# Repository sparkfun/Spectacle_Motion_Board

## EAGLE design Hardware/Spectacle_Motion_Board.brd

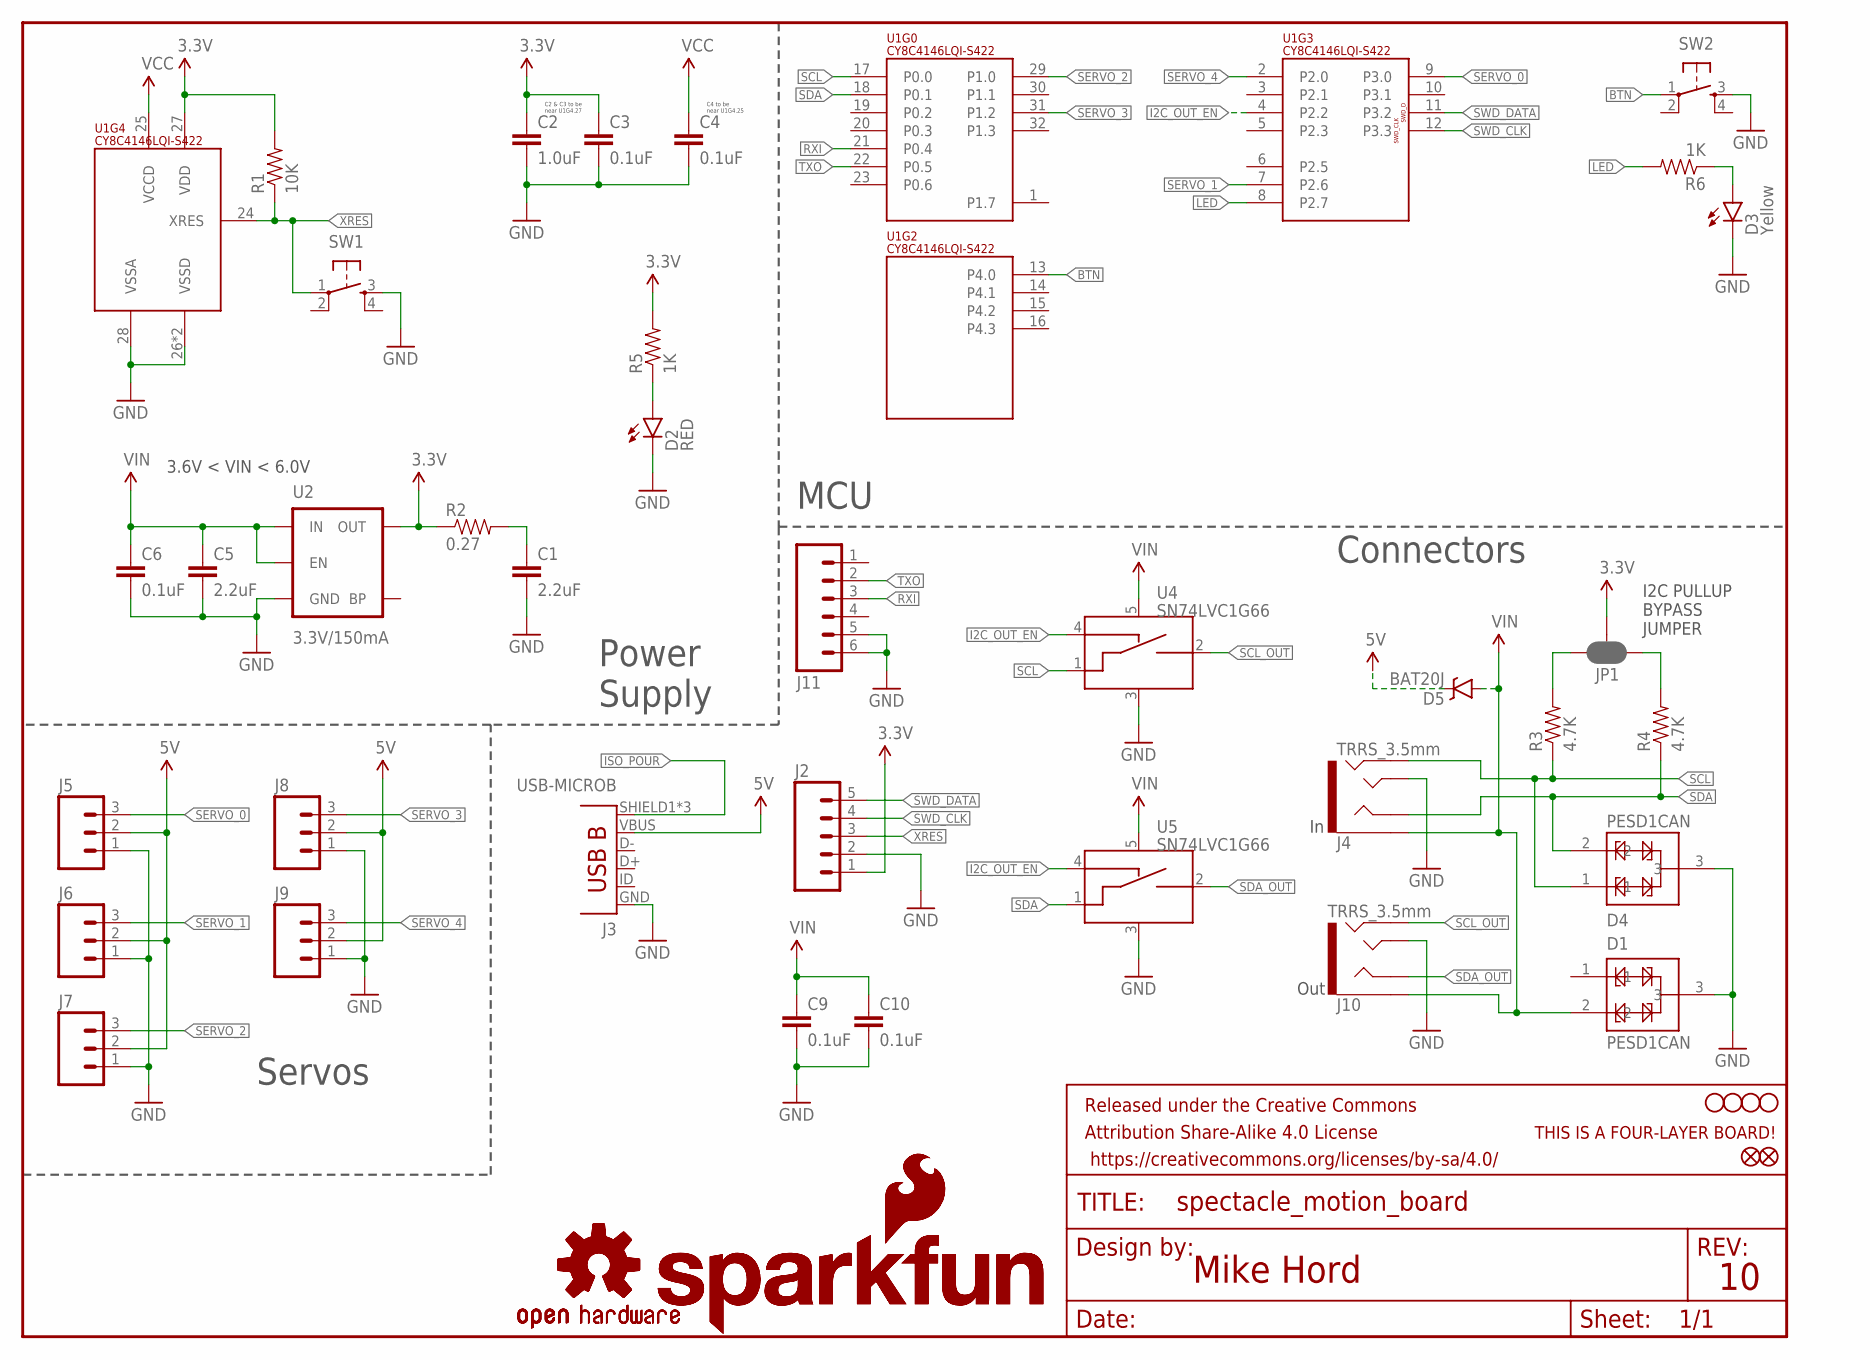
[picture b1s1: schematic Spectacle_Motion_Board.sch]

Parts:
C1, C5: 2.2uF; 0603-CAP
C2: 1.0uF; 0402-CAP
C3, C4, C6, C9, C10: 0.1uF; 0402-CAP
D1, D4: PESD1CAN; SOT23-3
D2: RED; LED-0603
D3: Yellow; LED-0603
D5: BAT20J; SOD-323
FD1, FD2: FIDUCIALUFIDUCIAL; MICRO-FIDUCIAL
FRAME1: FRAME-LETTER; CREATIVE_COMMONS
H1, H2, H3, H4: STAND-OFF
J2: M05NO_SILK; 1X05_NO_SILK
J3: USB-MICROB; USB-B-MICRO-SMD_V03_RED_PASTE
J4, J10: TRRS_3.5mm; AUDIO_JACK_3.5MM_TRRS_SMD_RA
J5, J6, J7, J8, J9: M03LOCK; 1X03_LOCK
J11: M06NO_SILK_NO_POP; 1X06_NO_SILK
JP1: JUMPER-PAD-3-NC_BY_PASTE; PAD-JUMPER-3-NC_BY_PASTE_YES_SILK_FULL_BOX
LOGO1, LOGO4: OSHW-LOGOS; OSHW-LOGO-S
LOGO2, LOGO3: SFE_LOGO_NAME_FLAME.1_INCH; SFE_LOGO_NAME_FLAME_.1
R1: 10K; 0603-RES
R2: 0.27; 0603-RES
R3, R4: 4.7K; 0603-RES
R5, R6: 1K; 0603-RES
SW1, SW2: SWITCH_SPST_4_PINRECT; TACTILE_SWITCH_SMD_4.6X2.8MM
U1: CY8C4146LQI-S422; QFN-32
U2: 3.3V/150mA; SOT23-5
U4, U5: SN74LVC1G66; SOT23-5
U$1: FOUR_LAYER_WARNING

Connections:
3.3V: C2.1, C3.1, J2.1, JP1.2, R1.2, R2.1, R5.2, U1.27 (VDD), U2.5 (OUT)
5V: D5.C, J3.VBUS, J5.2, J6.2, J7.2, J8.2, J9.2
BTN: SW2.1, U1.13 (P4.0)
GND: C1.2, C2.2, C3.2, C4.2, C5.2, C6.2, C9.2, C10.2, D1.3, D2.C, D3.C, D4.3, J2.2, J3.GND, J4.TIP, J5.1, J6.1, J7.1, J8.1, J9.1, J10.TIP, J11.5, J11.6, SW1.3, SW2.3, U1.26 (VSSD), U1.28 (VSSA), U1.EP (VSSD), U2.2 (GND), U4.3 (VSS), U5.3 (VSS)
I2C_OUT_EN: U1.4 (P2.2), U4.4 (CTRL_IN), U5.4 (CTRL_IN)
ISO_POUR: J3.SHIELD1 (SHIELD), J3.SHIELD2 (SHIELD), J3.SHIELD3 (SHIELD)
LED: R6.2, U1.8 (P2.7)
unnamed: JP1.3, R3.2
unnamed: C1.1, R2.2
unnamed: D2.A, R5.1
unnamed: D3.A, R6.1
unnamed: JP1.1, R4.2
RXI: J11.3, U1.21 (P0.4)
SCL: D4.1, J4.RING2, R3.1, U1.17 (P0.0), U4.1 (A_IN)
SCL_OUT: J10.RING2, U4.2 (A_OUT)
SDA: D4.2, J4.RING1, R4.1, U1.18 (P0.1), U5.1 (A_IN)
SDA_OUT: J10.RING1, U5.2 (A_OUT)
SERVO_0: J5.3, U1.9 (P3.0)
SERVO_1: J6.3, U1.7 (P2.6)
SERVO_2: J7.3, U1.29 (P1.0)
SERVO_3: J8.3, U1.31 (P1.2)
SERVO_4: J9.3, U1.2 (P2.0)
SWD_CLK: J2.4, U1.12 (P3.3)
SWD_DATA: J2.5, U1.11 (P3.2)
TXO: J11.2, U1.22 (P0.5)
VCC: C4.1, U1.25 (VCCD)
VIN: C5.1, C6.1, C9.1, C10.1, D1.2, D5.A, J4.EARTH, J10.EARTH, U2.1 (IN), U2.3 (EN), U4.5 (VCC), U5.5 (VCC)
XRES: J2.3, R1.1, SW1.1, U1.24 (XRES)

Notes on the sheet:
C2 & C3 to be near U1G4.27
C4 to be near U1G4.25
Mike Hord
MCU
Connectors
Servos
Power Supply
3.6V < VIN < 6.0V
I2C PULLUP BYPASS JUMPER
Out

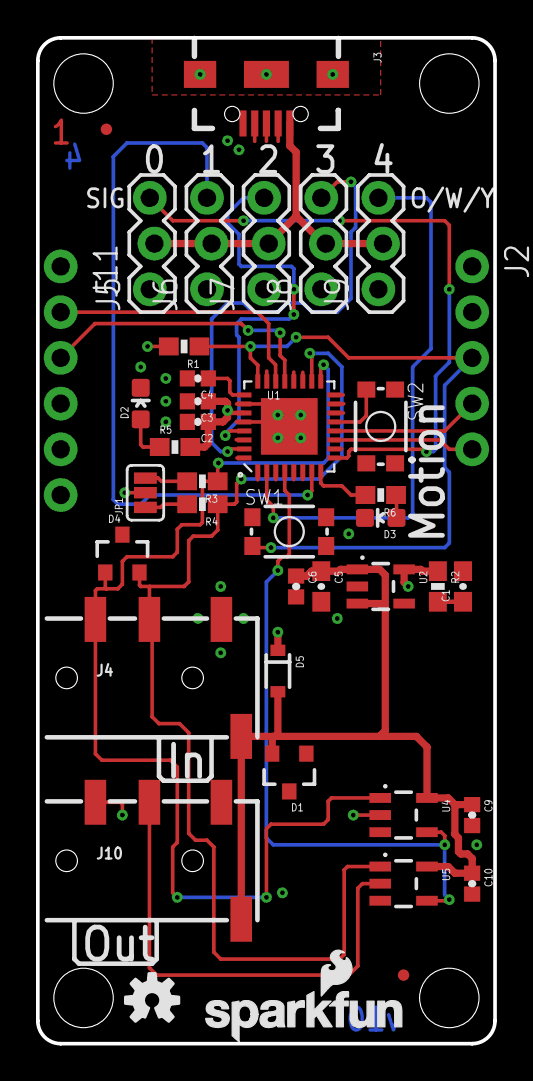
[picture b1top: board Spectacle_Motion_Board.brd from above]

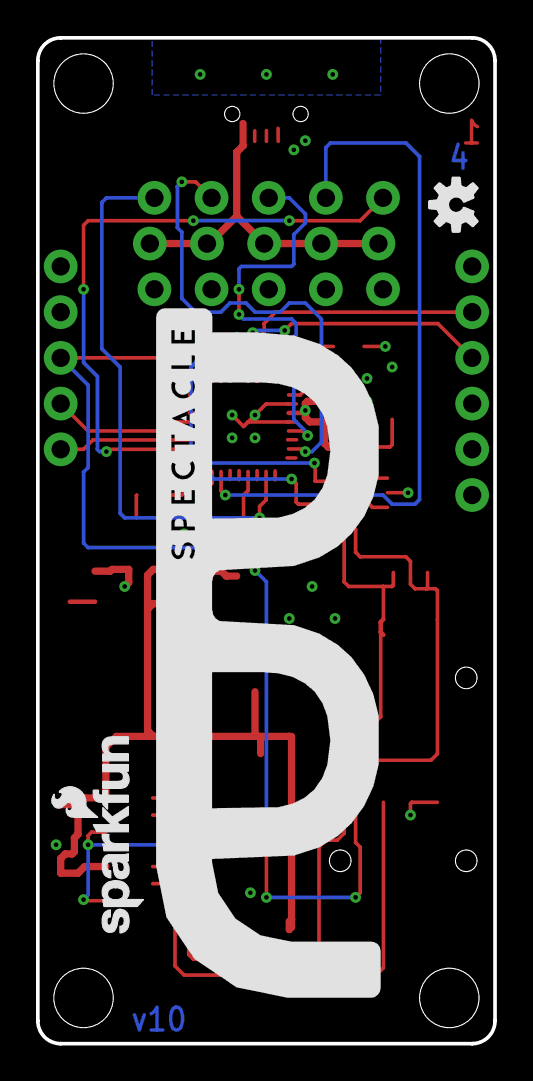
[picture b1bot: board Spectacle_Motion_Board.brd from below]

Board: 4 copper layers, 25.4 x 55.9 mm, 49 parts (3 on the bottom side), 28 nets.

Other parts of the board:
U$3: SPECTACLE_LOGO_NEGATIVE_1.5X0.5

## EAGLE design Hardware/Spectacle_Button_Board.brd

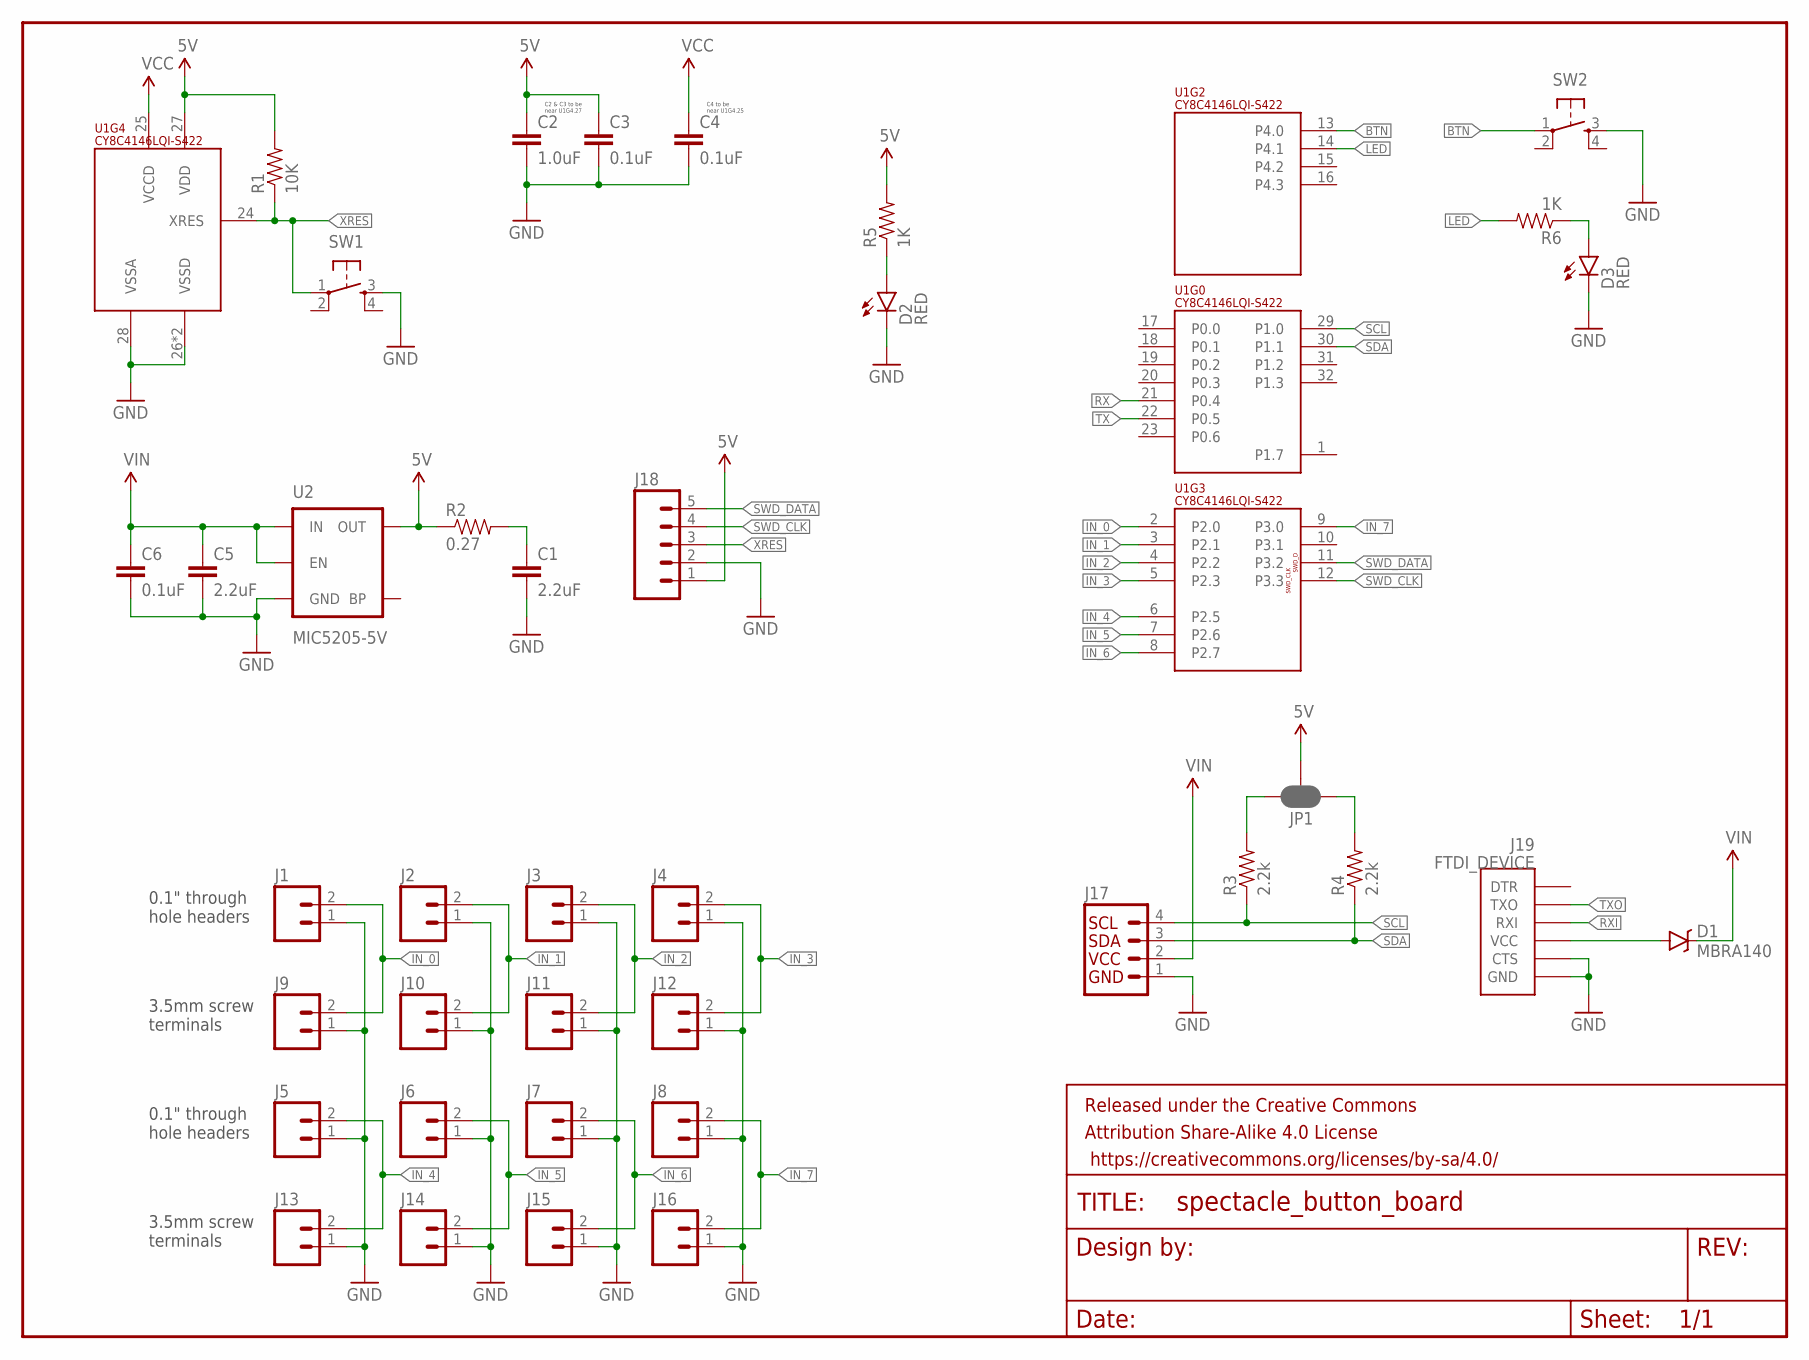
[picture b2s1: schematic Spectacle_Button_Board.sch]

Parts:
C1, C5: 2.2uF; 0603-CAP
C2: 1.0uF; 0402-CAP
C3, C4, C6: 0.1uF; 0402-CAP
D1: MBRA140; SMA-DIODE
D2, D3: RED; LED-0603
FRAME1: FRAME-LETTER; CREATIVE_COMMONS
J1, J2, J3, J4, J5, J6, J7, J8: M02PTH; 1X02
J9, J10, J11, J12, J13, J14, J15, J16: M023.5MM_LOCK; SCREWTERMINAL-3.5MM-2_LOCK
J17: I2C_STANDARD; 1X04
J18: M05PTH; 1X05
J19: FTDI_DEVICE; FTDI_DEVICE_SIDE
JP1: JUMPER-PAD-3-NC_BY_PASTE; PAD-JUMPER-3-NC_BY_PASTE_YES_SILK_FULL_BOX
R1: 10K; 0603-RES
R2: 0.27; 0603-RES
R3, R4: 2.2k; 0603-RES
R5, R6: 1K; 0603-RES
SW1, SW2: SWITCH_SPST_4_PINRECT; TACTILE_SWITCH_SMD_4.6X2.8MM
U1: CY8C4146LQI-S422; QFN-32
U2: MIC5205-5V; SOT23-5

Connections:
5V: C2.1, C3.1, J18.1, JP1.2, R1.2, R2.1, R5.2, U1.27 (VDD), U2.5 (OUT)
BTN: SW2.1, U1.13 (P4.0)
GND: C1.2, C2.2, C3.2, C4.2, C5.2, C6.2, D2.C, D3.C, J1.1, J2.1, J3.1, J4.1, J5.1, J6.1, J7.1, J8.1, J9.1, J10.1, J11.1, J12.1, J13.1, J14.1, J15.1, J16.1, J17.1, J18.2, J19.P$5 (CTS), J19.P$6 (GND), SW1.3, SW2.3, U1.26 (VSSD), U1.28 (VSSA), U1.EP (VSSD), U2.2 (GND)
IN_0: J1.2, J9.2, U1.2 (P2.0)
IN_1: J2.2, J10.2, U1.3 (P2.1)
IN_2: J3.2, J11.2, U1.4 (P2.2)
IN_3: J4.2, J12.2, U1.5 (P2.3)
IN_4: J5.2, J13.2, U1.6 (P2.5)
IN_5: J6.2, J14.2, U1.7 (P2.6)
IN_6: J7.2, J15.2, U1.8 (P2.7)
IN_7: J8.2, J16.2, U1.9 (P3.0)
LED: R6.2, U1.14 (P4.1)
unnamed: D1.A, J19.P$4 (VCC)
unnamed: JP1.3, R3.2
unnamed: C1.1, R2.2
unnamed: D2.A, R5.1
unnamed: D3.A, R6.1
unnamed: JP1.1, R4.2
RX: U1.21 (P0.4)
RXI: J19.P$3 (RXI)
SCL: J17.4, R3.1, U1.29 (P1.0)
SDA: J17.3, R4.1, U1.30 (P1.1)
SWD_CLK: J18.4, U1.12 (P3.3)
SWD_DATA: J18.5, U1.11 (P3.2)
TX: U1.22 (P0.5)
TXO: J19.P$2 (TXO)
VCC: C4.1, U1.25 (VCCD)
VIN: C5.1, C6.1, D1.C, J17.2, U2.1 (IN), U2.3 (EN)
XRES: J18.3, R1.1, SW1.1, U1.24 (XRES)

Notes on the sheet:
3.5mm screw terminals
0.1" through hole headers
C2 & C3 to be near U1G4.27
C4 to be near U1G4.25

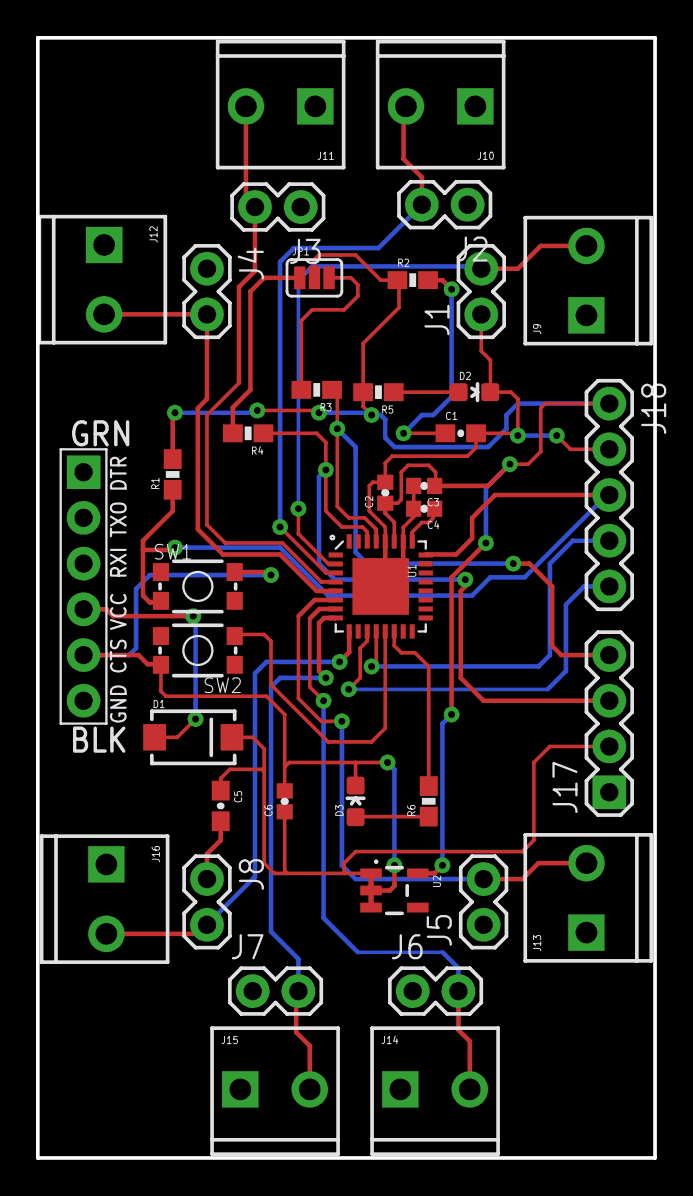
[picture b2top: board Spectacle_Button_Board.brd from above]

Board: 2 copper layers, 34.3 x 62.2 mm, 40 parts (0 on the bottom side), 25 nets.

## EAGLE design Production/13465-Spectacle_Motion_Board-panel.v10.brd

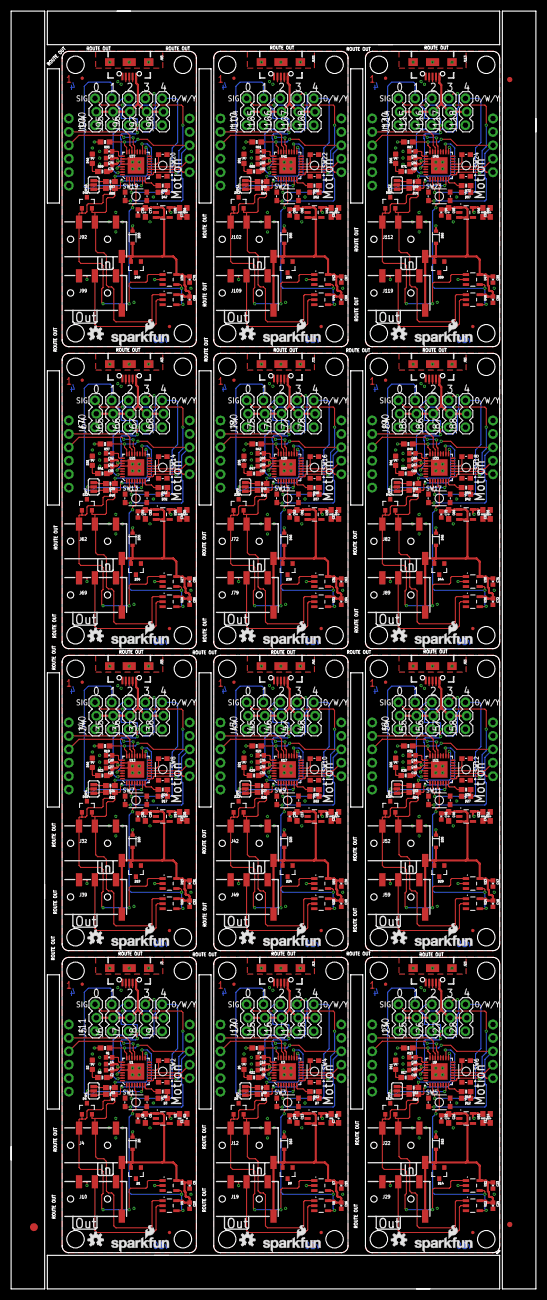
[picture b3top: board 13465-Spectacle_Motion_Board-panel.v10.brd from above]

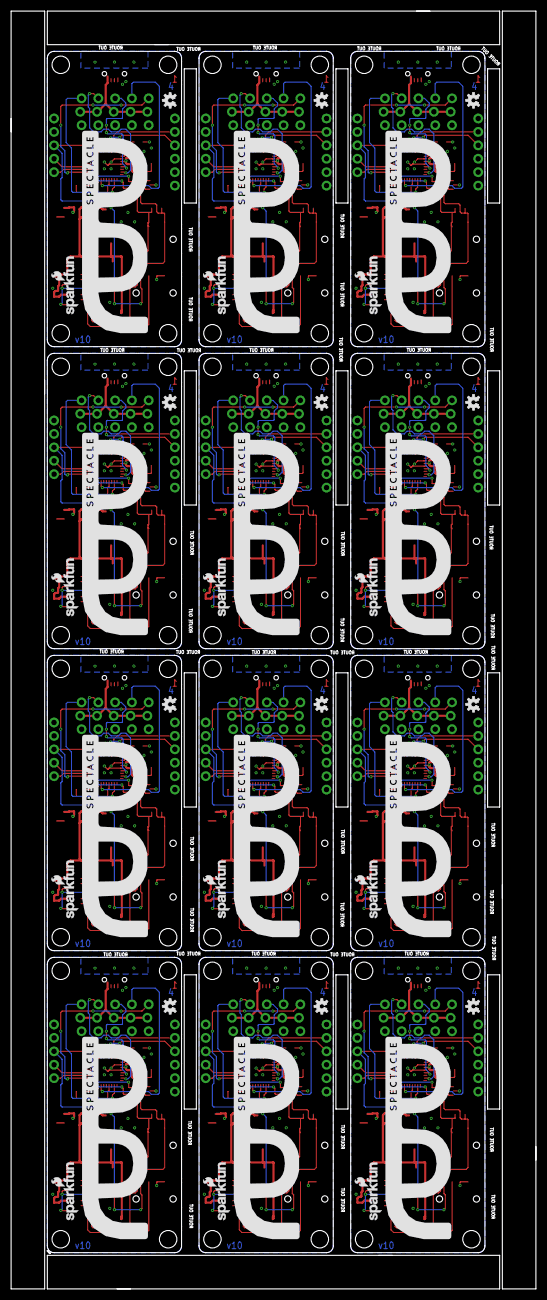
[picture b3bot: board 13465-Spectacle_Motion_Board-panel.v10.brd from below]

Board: 4 copper layers, 99.3 x 241.8 mm, 567 parts (36 on the bottom side), 336 nets.

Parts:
C1, C5, C7, C13, C17, C21, C25, C29, C33, C37, C41, C45, C49, C53, C57, C61, C65, C69, C73, C77, C81, C85, C89, C93: 2.2uF; 0603-CAP
C2, C8, C18, C26, C34, C42, C50, C58, C66, C74, C82, C90: 1.0uF; 0402-CAP
C3, C4, C6, C9, C10, C11, C12, C14, C15, C16, C19, C20, C22, C23, C24, C27, C28, C30, C31, C32, C35, C36, C38, C39, C40, C43, C44, C46, C47, C48, C51, C52, C54, C55, C56, C59, C60, C62, C63, C64, C67, C68, C70, C71, C72, C75, C76, C78, C79, C80, C83, C84, C86, C87, C88, C91, C92, C94, C95, C96: 0.1uF; 0402-CAP
D1, D4, D8, D9, D13, D14, D18, D19, D23, D24, D28, D29, D33, D34, D38, D39, D43, D44, D48, D49, D53, D54, D58, D59: PESD1CAN; SOT23-3
D2, D6, D11, D16, D21, D26, D31, D36, D41, D46, D51, D56: RED; LED-0603
D3, D7, D12, D17, D22, D27, D32, D37, D42, D47, D52, D57: Yellow; LED-0603
D5, D10, D15, D20, D25, D30, D35, D40, D45, D50, D55, D60: BAT20J; SOD-323
E$1: FIDUCIAL-1.5X3
E$7, E$8: FIDUCIAL-1X2
FD1, FD2, FD3, FD4, FD5, FD6, FD7, FD8, FD9, FD10, FD11, FD12, FD13, FD14, FD15, FD16, FD17, FD18, FD19, FD20, FD21, FD22, FD23, FD24: FIDUCIALUFIDUCIAL; MICRO-FIDUCIAL
H1, H2, H3, H4, H5, H6, H7, H8, H9, H10, H11, H12, H13, H14, H15, H16, H17, H18, H19, H20, H21, H22, H23, H24, H25, H26, H27, H28, H29, H30, H31, H32, H33, H34, H35, H36, H37, H38, H39, H40, H41, H42, H43, H44, H45, H46, H47, H48: STAND-OFF
J1, J2, J21, J31, J41, J51, J61, J71, J81, J91, J101, J111: 1X05_NO_SILK
J3, J13, J23, J33, J43, J53, J63, J73, J83, J93, J103, J113: USB-MICROB; USB-B-MICRO-SMD_V03_RED_PASTE
J4, J10, J12, J19, J22, J29, J32, J39, J42, J49, J52, J59, J62, J69, J72, J79, J82, J89, J92, J99, J102, J109, J112, J119: TRRS_3.5mm; AUDIO_JACK_3.5MM_TRRS_SMD_RA
J5, J6, J7, J8, J9, J14, J15, J16, J17, J18, J24, J25, J26, J27, J28, J34, J35, J36, J37, J38, J44, J45, J46, J47, J48, J54, J55, J56, J57, J58, J64, J65, J66, J67, J68, J74, J75, J76, J77, J78, J84, J85, J86, J87, J88, J94, J95, J96, J97, J98, J104, J105, J106, J107, J108, J114, J115, J116, J117, J118: 1X03_LOCK
J11, J20, J30, J40, J50, J60, J70, J80, J90, J100, J110, J120: 1X06_NO_SILK
JP1, JP2, JP3, JP4, JP5, JP6, JP7, JP8, JP9, JP10, JP11, JP12: JUMPER-PAD-3-NC_BY_PASTE; PAD-JUMPER-3-NC_BY_PASTE_YES_SILK_FULL_BOX
LOGO1, LOGO4, LOGO5, LOGO8, LOGO9, LOGO12, LOGO13, LOGO16, LOGO17, LOGO20, LOGO21, LOGO24, LOGO25, LOGO28, LOGO29, LOGO32, LOGO33, LOGO36, LOGO37, LOGO40, LOGO41, LOGO44, LOGO45, LOGO48: OSHW-LOGOS; OSHW-LOGO-S
LOGO2, LOGO3, LOGO6, LOGO7, LOGO10, LOGO11, LOGO14, LOGO15, LOGO18, LOGO19, LOGO22, LOGO23, LOGO26, LOGO27, LOGO30, LOGO31, LOGO34, LOGO35, LOGO38, LOGO39, LOGO42, LOGO43, LOGO46, LOGO47: SFE_LOGO_NAME_FLAME.1_INCH; SFE_LOGO_NAME_FLAME_.1
R1, R7, R13, R19, R25, R31, R37, R43, R49, R55, R61, R67: 10K; 0603-RES
R2, R8, R14, R20, R26, R32, R38, R44, R50, R56, R62, R68: 0.27; 0603-RES
R3, R4, R9, R10, R15, R16, R21, R22, R27, R28, R33, R34, R39, R40, R45, R46, R51, R52, R57, R58, R63, R64, R69, R70: 4.7K; 0603-RES
R5, R6, R11, R12, R17, R18, R23, R24, R29, R30, R35, R36, R41, R42, R47, R48, R53, R54, R59, R60, R65, R66, R71, R72: 1K; 0603-RES
SW1, SW2, SW3, SW4, SW5, SW6, SW7, SW8, SW9, SW10, SW11, SW12, SW13, SW14, SW15, SW16, SW17, SW18, SW19, SW20, SW21, SW22, SW23, SW24: TACTILE_SWITCH_SMD_4.6X2.8MM
U1, U3, U9, U13, U17, U21, U25, U29, U33, U37, U41, U45: CY8C4146LQI-S422; QFN-32
U2, U6, U10, U14, U18, U22, U26, U30, U34, U38, U42, U46: 3.3V/150mA; SOT23-5
U4, U5, U7, U8, U11, U12, U15, U16, U19, U20, U23, U24, U27, U28, U31, U32, U35, U36, U39, U40, U43, U44, U47, U48: SN74LVC1G66; SOT23-5
U$1, U$2, U$3, U$4, U$5, U$6, U$7, U$8, U$9, U$10, U$11, U$12: SPECTACLE_LOGO_NEGATIVE_1.5X0.5

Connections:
3.3V: C2.1, C3.1, J2.1, JP1.2, R1.2, R2.1, R5.2, U1.27, U2.5
3.3V1: C8.1, C11.1, J1.1, JP2.2, R7.2, R8.1, R11.2, U3.27, U6.5
3.3V2: C18.1, C19.1, J21.1, JP3.2, R13.2, R14.1, R17.2, U9.27, U10.5
3.3V3: C26.1, C27.1, J31.1, JP4.2, R19.2, R20.1, R23.2, U13.27, U14.5
3.3V4: C34.1, C35.1, J41.1, JP5.2, R25.2, R26.1, R29.2, U17.27, U18.5
3.3V5: C42.1, C43.1, J51.1, JP6.2, R31.2, R32.1, R35.2, U21.27, U22.5
3.3V6: C50.1, C51.1, J61.1, JP7.2, R37.2, R38.1, R41.2, U25.27, U26.5
3.3V7: C58.1, C59.1, J71.1, JP8.2, R43.2, R44.1, R47.2, U29.27, U30.5
3.3V8: C66.1, C67.1, J81.1, JP9.2, R49.2, R50.1, R53.2, U33.27, U34.5
3.3V9: C74.1, C75.1, J91.1, JP10.2, R55.2, R56.1, R59.2, U37.27, U38.5
3.3V10: C82.1, C83.1, J101.1, JP11.2, R61.2, R62.1, R65.2, U41.27, U42.5
3.3V11: C90.1, C91.1, J111.1, JP12.2, R67.2, R68.1, R71.2, U45.27, U46.5
5V: D5.C, J3.VBUS, J5.2, J6.2, J7.2, J8.2, J9.2
5V1: D10.C, J13.VBUS, J14.2, J15.2, J16.2, J17.2, J18.2
5V2: D15.C, J23.VBUS, J24.2, J25.2, J26.2, J27.2, J28.2
5V3: D20.C, J33.VBUS, J34.2, J35.2, J36.2, J37.2, J38.2
5V4: D25.C, J43.VBUS, J44.2, J45.2, J46.2, J47.2, J48.2
5V5: D30.C, J53.VBUS, J54.2, J55.2, J56.2, J57.2, J58.2
5V6: D35.C, J63.VBUS, J64.2, J65.2, J66.2, J67.2, J68.2
5V7: D40.C, J73.VBUS, J74.2, J75.2, J76.2, J77.2, J78.2
5V8: D45.C, J83.VBUS, J84.2, J85.2, J86.2, J87.2, J88.2
5V9: D50.C, J93.VBUS, J94.2, J95.2, J96.2, J97.2, J98.2
5V10: D55.C, J103.VBUS, J104.2, J105.2, J106.2, J107.2, J108.2
5V11: D60.C, J113.VBUS, J114.2, J115.2, J116.2, J117.2, J118.2
BTN: SW2.1, U1.13
BTN1: SW4.1, U3.13
BTN2: SW6.1, U9.13
BTN3: SW8.1, U13.13
BTN4: SW10.1, U17.13
BTN5: SW12.1, U21.13
BTN6: SW14.1, U25.13
BTN7: SW16.1, U29.13
BTN8: SW18.1, U33.13
BTN9: SW20.1, U37.13
BTN10: SW22.1, U41.13
BTN11: SW24.1, U45.13
GND: C1.2, C2.2, C3.2, C4.2, C5.2, C6.2, C9.2, C10.2, D1.3, D2.C, D3.C, D4.3, J2.2, J3.GND, J4.TIP, J5.1, J6.1, J7.1, J8.1, J9.1, J10.TIP, J11.5, J11.6, SW1.3, SW2.3, U1.26, U1.28, U1.EP, U2.2, U4.3, U5.3
GND1: C7.2, C8.2, C11.2, C12.2, C13.2, C14.2, C15.2, C16.2, D6.C, D7.C, D8.3, D9.3, J1.2, J12.TIP, J13.GND, J14.1, J15.1, J16.1, J17.1, J18.1, J19.TIP, J20.5, J20.6, SW3.3, SW4.3, U3.26, U3.28, U3.EP, U6.2, U7.3, U8.3
GND2: C17.2, C18.2, C19.2, C20.2, C21.2, C22.2, C23.2, C24.2, D11.C, D12.C, D13.3, D14.3, J21.2, J22.TIP, J23.GND, J24.1, J25.1, J26.1, J27.1, J28.1, J29.TIP, J30.5, J30.6, SW5.3, SW6.3, U9.26, U9.28, U9.EP, U10.2, U11.3, U12.3
GND3: C25.2, C26.2, C27.2, C28.2, C29.2, C30.2, C31.2, C32.2, D16.C, D17.C, D18.3, D19.3, J31.2, J32.TIP, J33.GND, J34.1, J35.1, J36.1, J37.1, J38.1, J39.TIP, J40.5, J40.6, SW7.3, SW8.3, U13.26, U13.28, U13.EP, U14.2, U15.3, U16.3
GND4: C33.2, C34.2, C35.2, C36.2, C37.2, C38.2, C39.2, C40.2, D21.C, D22.C, D23.3, D24.3, J41.2, J42.TIP, J43.GND, J44.1, J45.1, J46.1, J47.1, J48.1, J49.TIP, J50.5, J50.6, SW9.3, SW10.3, U17.26, U17.28, U17.EP, U18.2, U19.3, U20.3
GND5: C41.2, C42.2, C43.2, C44.2, C45.2, C46.2, C47.2, C48.2, D26.C, D27.C, D28.3, D29.3, J51.2, J52.TIP, J53.GND, J54.1, J55.1, J56.1, J57.1, J58.1, J59.TIP, J60.5, J60.6, SW11.3, SW12.3, U21.26, U21.28, U21.EP, U22.2, U23.3, U24.3
GND6: C49.2, C50.2, C51.2, C52.2, C53.2, C54.2, C55.2, C56.2, D31.C, D32.C, D33.3, D34.3, J61.2, J62.TIP, J63.GND, J64.1, J65.1, J66.1, J67.1, J68.1, J69.TIP, J70.5, J70.6, SW13.3, SW14.3, U25.26, U25.28, U25.EP, U26.2, U27.3, U28.3
GND7: C57.2, C58.2, C59.2, C60.2, C61.2, C62.2, C63.2, C64.2, D36.C, D37.C, D38.3, D39.3, J71.2, J72.TIP, J73.GND, J74.1, J75.1, J76.1, J77.1, J78.1, J79.TIP, J80.5, J80.6, SW15.3, SW16.3, U29.26, U29.28, U29.EP, U30.2, U31.3, U32.3
GND8: C65.2, C66.2, C67.2, C68.2, C69.2, C70.2, C71.2, C72.2, D41.C, D42.C, D43.3, D44.3, J81.2, J82.TIP, J83.GND, J84.1, J85.1, J86.1, J87.1, J88.1, J89.TIP, J90.5, J90.6, SW17.3, SW18.3, U33.26, U33.28, U33.EP, U34.2, U35.3, U36.3
GND9: C73.2, C74.2, C75.2, C76.2, C77.2, C78.2, C79.2, C80.2, D46.C, D47.C, D48.3, D49.3, J91.2, J92.TIP, J93.GND, J94.1, J95.1, J96.1, J97.1, J98.1, J99.TIP, J100.5, J100.6, SW19.3, SW20.3, U37.26, U37.28, U37.EP, U38.2, U39.3, U40.3
GND10: C81.2, C82.2, C83.2, C84.2, C85.2, C86.2, C87.2, C88.2, D51.C, D52.C, D53.3, D54.3, J101.2, J102.TIP, J103.GND, J104.1, J105.1, J106.1, J107.1, J108.1, J109.TIP, J110.5, J110.6, SW21.3, SW22.3, U41.26, U41.28, U41.EP, U42.2, U43.3, U44.3
GND11: C89.2, C90.2, C91.2, C92.2, C93.2, C94.2, C95.2, C96.2, D56.C, D57.C, D58.3, D59.3, J111.2, J112.TIP, J113.GND, J114.1, J115.1, J116.1, J117.1, J118.1, J119.TIP, J120.5, J120.6, SW23.3, SW24.3, U45.26, U45.28, U45.EP, U46.2, U47.3, U48.3
I2C_OUT_EN: U1.4, U4.4, U5.4
I2C_OUT_EN1: U3.4, U7.4, U8.4
I2C_OUT_EN2: U9.4, U11.4, U12.4
I2C_OUT_EN3: U13.4, U15.4, U16.4
I2C_OUT_EN4: U17.4, U19.4, U20.4
I2C_OUT_EN5: U21.4, U23.4, U24.4
I2C_OUT_EN6: U25.4, U27.4, U28.4
I2C_OUT_EN7: U29.4, U31.4, U32.4
I2C_OUT_EN8: U33.4, U35.4, U36.4
I2C_OUT_EN9: U37.4, U39.4, U40.4
I2C_OUT_EN10: U41.4, U43.4, U44.4
I2C_OUT_EN11: U45.4, U47.4, U48.4
ISO_POUR: J3.SHIELD1, J3.SHIELD2, J3.SHIELD3
ISO_POUR1: J13.SHIELD1, J13.SHIELD2, J13.SHIELD3
ISO_POUR2: J23.SHIELD1, J23.SHIELD2, J23.SHIELD3
ISO_POUR3: J33.SHIELD1, J33.SHIELD2, J33.SHIELD3
ISO_POUR4: J43.SHIELD1, J43.SHIELD2, J43.SHIELD3
ISO_POUR5: J53.SHIELD1, J53.SHIELD2, J53.SHIELD3
ISO_POUR6: J63.SHIELD1, J63.SHIELD2, J63.SHIELD3
ISO_POUR7: J73.SHIELD1, J73.SHIELD2, J73.SHIELD3
ISO_POUR8: J83.SHIELD1, J83.SHIELD2, J83.SHIELD3
ISO_POUR9: J93.SHIELD1, J93.SHIELD2, J93.SHIELD3
ISO_POUR10: J103.SHIELD1, J103.SHIELD2, J103.SHIELD3
ISO_POUR11: J113.SHIELD1, J113.SHIELD2, J113.SHIELD3
LED: R6.2, U1.8
LED1: R12.2, U3.8
LED2: R18.2, U9.8
LED3: R24.2, U13.8
LED4: R30.2, U17.8
LED5: R36.2, U21.8
LED6: R42.2, U25.8
LED7: R48.2, U29.8
LED8: R54.2, U33.8
LED9: R60.2, U37.8
LED10: R66.2, U41.8
LED11: R72.2, U45.8
unnamed: JP1.3, R3.2
unnamed: C1.1, R2.2
unnamed: D2.A, R5.1
unnamed: D3.A, R6.1
unnamed: JP1.1, R4.2
unnamed: C7.1, R8.2
unnamed: JP2.3, R9.2
unnamed: JP2.1, R10.2
unnamed: D6.A, R11.1
unnamed: D7.A, R12.1
unnamed: C17.1, R14.2
unnamed: JP3.3, R15.2
unnamed: JP3.1, R16.2
unnamed: D11.A, R17.1
unnamed: D12.A, R18.1
unnamed: C25.1, R20.2
unnamed: JP4.3, R21.2
unnamed: JP4.1, R22.2
unnamed: D16.A, R23.1
unnamed: D17.A, R24.1
unnamed: C33.1, R26.2
unnamed: JP5.3, R27.2
unnamed: JP5.1, R28.2
unnamed: D21.A, R29.1
unnamed: D22.A, R30.1
unnamed: C41.1, R32.2
unnamed: JP6.3, R33.2
unnamed: JP6.1, R34.2
unnamed: D26.A, R35.1
unnamed: D27.A, R36.1
unnamed: C49.1, R38.2
unnamed: JP7.3, R39.2
unnamed: JP7.1, R40.2
unnamed: D31.A, R41.1
unnamed: D32.A, R42.1
unnamed: C57.1, R44.2
unnamed: JP8.3, R45.2
unnamed: JP8.1, R46.2
unnamed: D36.A, R47.1
unnamed: D37.A, R48.1
unnamed: C65.1, R50.2
unnamed: JP9.3, R51.2
unnamed: JP9.1, R52.2
unnamed: D41.A, R53.1
unnamed: D42.A, R54.1
unnamed: C73.1, R56.2
unnamed: JP10.3, R57.2
unnamed: JP10.1, R58.2
unnamed: D46.A, R59.1
unnamed: D47.A, R60.1
unnamed: C81.1, R62.2
unnamed: JP11.3, R63.2
unnamed: JP11.1, R64.2
unnamed: D51.A, R65.1
unnamed: D52.A, R66.1
unnamed: C89.1, R68.2
unnamed: JP12.3, R69.2
unnamed: JP12.1, R70.2
unnamed: D56.A, R71.1
unnamed: D57.A, R72.1
RXI: J11.3, U1.21
RXI1: J20.3, U3.21
RXI2: J30.3, U9.21
RXI3: J40.3, U13.21
RXI4: J50.3, U17.21
RXI5: J60.3, U21.21
RXI6: J70.3, U25.21
RXI7: J80.3, U29.21
RXI8: J90.3, U33.21
RXI9: J100.3, U37.21
RXI10: J110.3, U41.21
RXI11: J120.3, U45.21
SCL: D4.1, J4.RING2, R3.1, U1.17, U4.1
SCL1: D8.1, J12.RING2, R9.1, U3.17, U7.1
SCL2: D13.1, J22.RING2, R15.1, U9.17, U11.1
SCL3: D18.1, J32.RING2, R21.1, U13.17, U15.1
SCL4: D23.1, J42.RING2, R27.1, U17.17, U19.1
SCL5: D28.1, J52.RING2, R33.1, U21.17, U23.1
SCL6: D33.1, J62.RING2, R39.1, U25.17, U27.1
SCL7: D38.1, J72.RING2, R45.1, U29.17, U31.1
SCL8: D43.1, J82.RING2, R51.1, U33.17, U35.1
SCL9: D48.1, J92.RING2, R57.1, U37.17, U39.1
SCL10: D53.1, J102.RING2, R63.1, U41.17, U43.1
SCL11: D58.1, J112.RING2, R69.1, U45.17, U47.1
SCL_OUT: J10.RING2, U4.2
SCL_OUT1: J19.RING2, U7.2
SCL_OUT2: J29.RING2, U11.2
SCL_OUT3: J39.RING2, U15.2
SCL_OUT4: J49.RING2, U19.2
SCL_OUT5: J59.RING2, U23.2
SCL_OUT6: J69.RING2, U27.2
SCL_OUT7: J79.RING2, U31.2
SCL_OUT8: J89.RING2, U35.2
SCL_OUT9: J99.RING2, U39.2
SCL_OUT10: J109.RING2, U43.2
SCL_OUT11: J119.RING2, U47.2
SDA: D4.2, J4.RING1, R4.1, U1.18, U5.1
SDA1: D8.2, J12.RING1, R10.1, U3.18, U8.1
SDA2: D13.2, J22.RING1, R16.1, U9.18, U12.1
SDA3: D18.2, J32.RING1, R22.1, U13.18, U16.1
SDA4: D23.2, J42.RING1, R28.1, U17.18, U20.1
SDA5: D28.2, J52.RING1, R34.1, U21.18, U24.1
SDA6: D33.2, J62.RING1, R40.1, U25.18, U28.1
SDA7: D38.2, J72.RING1, R46.1, U29.18, U32.1
SDA8: D43.2, J82.RING1, R52.1, U33.18, U36.1
SDA9: D48.2, J92.RING1, R58.1, U37.18, U40.1
SDA10: D53.2, J102.RING1, R64.1, U41.18, U44.1
SDA11: D58.2, J112.RING1, R70.1, U45.18, U48.1
SDA_OUT: J10.RING1, U5.2
SDA_OUT1: J19.RING1, U8.2
SDA_OUT2: J29.RING1, U12.2
SDA_OUT3: J39.RING1, U16.2
SDA_OUT4: J49.RING1, U20.2
SDA_OUT5: J59.RING1, U24.2
SDA_OUT6: J69.RING1, U28.2
SDA_OUT7: J79.RING1, U32.2
SDA_OUT8: J89.RING1, U36.2
SDA_OUT9: J99.RING1, U40.2
SDA_OUT10: J109.RING1, U44.2
SDA_OUT11: J119.RING1, U48.2
SERVO_0: J5.3, U1.9
SERVO_1: J6.3, U1.7
SERVO_2: J7.3, U1.29
SERVO_3: J8.3, U1.31
SERVO_4: J9.3, U1.2
SERVO_5: J14.3, U3.9
SERVO_6: J15.3, U3.7
SERVO_7: J16.3, U3.29
SERVO_8: J17.3, U3.31
SERVO_9: J18.3, U3.2
SERVO_10: J24.3, U9.9
SERVO_11: J25.3, U9.7
SERVO_12: J26.3, U9.29
SERVO_13: J27.3, U9.31
SERVO_14: J28.3, U9.2
SERVO_15: J34.3, U13.9
SERVO_16: J35.3, U13.7
SERVO_17: J36.3, U13.29
SERVO_18: J37.3, U13.31
SERVO_19: J38.3, U13.2
SERVO_20: J44.3, U17.9
SERVO_21: J45.3, U17.7
SERVO_22: J46.3, U17.29
SERVO_23: J47.3, U17.31
SERVO_24: J48.3, U17.2
SERVO_25: J54.3, U21.9
SERVO_26: J55.3, U21.7
SERVO_27: J56.3, U21.29
SERVO_28: J57.3, U21.31
SERVO_29: J58.3, U21.2
SERVO_30: J64.3, U25.9
SERVO_31: J65.3, U25.7
SERVO_32: J66.3, U25.29
SERVO_33: J67.3, U25.31
SERVO_34: J68.3, U25.2
SERVO_35: J74.3, U29.9
SERVO_36: J75.3, U29.7
SERVO_37: J76.3, U29.29
SERVO_38: J77.3, U29.31
SERVO_39: J78.3, U29.2
SERVO_40: J84.3, U33.9
SERVO_41: J85.3, U33.7
SERVO_42: J86.3, U33.29
SERVO_43: J87.3, U33.31
SERVO_44: J88.3, U33.2
SERVO_45: J94.3, U37.9
SERVO_46: J95.3, U37.7
SERVO_47: J96.3, U37.29
SERVO_48: J97.3, U37.31
SERVO_49: J98.3, U37.2
SERVO_50: J104.3, U41.9
SERVO_51: J105.3, U41.7
SERVO_52: J106.3, U41.29
SERVO_53: J107.3, U41.31
SERVO_54: J108.3, U41.2
SERVO_55: J114.3, U45.9
SERVO_56: J115.3, U45.7
SERVO_57: J116.3, U45.29
SERVO_58: J117.3, U45.31
SERVO_59: J118.3, U45.2
SWD_CLK: J2.4, U1.12
SWD_CLK1: J1.4, U3.12
SWD_CLK2: J21.4, U9.12
SWD_CLK3: J31.4, U13.12
SWD_CLK4: J41.4, U17.12
SWD_CLK5: J51.4, U21.12
SWD_CLK6: J61.4, U25.12
SWD_CLK7: J71.4, U29.12
SWD_CLK8: J81.4, U33.12
SWD_CLK9: J91.4, U37.12
SWD_CLK10: J101.4, U41.12
SWD_CLK11: J111.4, U45.12
SWD_DATA: J2.5, U1.11
SWD_DATA1: J1.5, U3.11
SWD_DATA2: J21.5, U9.11
SWD_DATA3: J31.5, U13.11
SWD_DATA4: J41.5, U17.11
SWD_DATA5: J51.5, U21.11
SWD_DATA6: J61.5, U25.11
SWD_DATA7: J71.5, U29.11
SWD_DATA8: J81.5, U33.11
SWD_DATA9: J91.5, U37.11
SWD_DATA10: J101.5, U41.11
SWD_DATA11: J111.5, U45.11
TXO: J11.2, U1.22
TXO1: J20.2, U3.22
TXO2: J30.2, U9.22
TXO3: J40.2, U13.22
TXO4: J50.2, U17.22
TXO5: J60.2, U21.22
TXO6: J70.2, U25.22
TXO7: J80.2, U29.22
TXO8: J90.2, U33.22
TXO9: J100.2, U37.22
TXO10: J110.2, U41.22
TXO11: J120.2, U45.22
VCC: C4.1, U1.25
VCC1: C12.1, U3.25
VCC2: C20.1, U9.25
VCC3: C28.1, U13.25
VCC4: C36.1, U17.25
VCC5: C44.1, U21.25
VCC6: C52.1, U25.25
VCC7: C60.1, U29.25
VCC8: C68.1, U33.25
VCC9: C76.1, U37.25
VCC10: C84.1, U41.25
VCC11: C92.1, U45.25
VIN: C5.1, C6.1, C9.1, C10.1, D1.2, D5.A, J4.EARTH, J10.EARTH, U2.1, U2.3, U4.5, U5.5
VIN1: C13.1, C14.1, C15.1, C16.1, D9.2, D10.A, J12.EARTH, J19.EARTH, U6.1, U6.3, U7.5, U8.5
VIN2: C21.1, C22.1, C23.1, C24.1, D14.2, D15.A, J22.EARTH, J29.EARTH, U10.1, U10.3, U11.5, U12.5
VIN3: C29.1, C30.1, C31.1, C32.1, D19.2, D20.A, J32.EARTH, J39.EARTH, U14.1, U14.3, U15.5, U16.5
VIN4: C37.1, C38.1, C39.1, C40.1, D24.2, D25.A, J42.EARTH, J49.EARTH, U18.1, U18.3, U19.5, U20.5
VIN5: C45.1, C46.1, C47.1, C48.1, D29.2, D30.A, J52.EARTH, J59.EARTH, U22.1, U22.3, U23.5, U24.5
VIN6: C53.1, C54.1, C55.1, C56.1, D34.2, D35.A, J62.EARTH, J69.EARTH, U26.1, U26.3, U27.5, U28.5
VIN7: C61.1, C62.1, C63.1, C64.1, D39.2, D40.A, J72.EARTH, J79.EARTH, U30.1, U30.3, U31.5, U32.5
VIN8: C69.1, C70.1, C71.1, C72.1, D44.2, D45.A, J82.EARTH, J89.EARTH, U34.1, U34.3, U35.5, U36.5
VIN9: C77.1, C78.1, C79.1, C80.1, D49.2, D50.A, J92.EARTH, J99.EARTH, U38.1, U38.3, U39.5, U40.5
VIN10: C85.1, C86.1, C87.1, C88.1, D54.2, D55.A, J102.EARTH, J109.EARTH, U42.1, U42.3, U43.5, U44.5
VIN11: C93.1, C94.1, C95.1, C96.1, D59.2, D60.A, J112.EARTH, J119.EARTH, U46.1, U46.3, U47.5, U48.5
XRES: J2.3, R1.1, SW1.1, U1.24
XRES1: J1.3, R7.1, SW3.1, U3.24
XRES2: J21.3, R13.1, SW5.1, U9.24
XRES3: J31.3, R19.1, SW7.1, U13.24
XRES4: J41.3, R25.1, SW9.1, U17.24
XRES5: J51.3, R31.1, SW11.1, U21.24
XRES6: J61.3, R37.1, SW13.1, U25.24
XRES7: J71.3, R43.1, SW15.1, U29.24
XRES8: J81.3, R49.1, SW17.1, U33.24
XRES9: J91.3, R55.1, SW19.1, U37.24
XRES10: J101.3, R61.1, SW21.1, U41.24
XRES11: J111.3, R67.1, SW23.1, U45.24

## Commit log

2016-03-21 Added LED, buttons
2016-05-11 Laid out board
2016-07-15 Derived from Button Board
2016-07-18 Okay'ed some DRC errors
2016-08-01 Changes from design review, initial checklist pass
2016-08-02 Revised from feedback from QC
2016-09-14 Firmware check-in Contains a test firmware for Arduino and an intermediate working firmware for the Spectacle board which can receive over I2C and respond to commands sent over I2C.
2016-10-11 Added downstream power control circuitry
2016-10-19 Add servo.h, .project, in/out labels
2016-10-25 Change board and repo name
2016-10-25 Feedback from review incorporated, ready for qc review
2016-10-31 Chg I2C pullup value
2016-11-01 Feedback from reviews incorporated
2016-11-01 Increased inner pour coverage
2016-11-01 Added and fixed some product IDs
2016-11-11 Implemented mailboxing for firmware
2016-11-18 Firmware check-in - Implementation of trigger-by-channel complete - Implementation of behavior programming complete - Abstraction of behaviors from main() complete
2016-12-20 Firmware commit All functionality present and passes initial test
2017-01-23 Touchups for v10
2017-01-25 Tidying up for release - Removed some unneeded files and code - Added headers to all files
2017-01-25 Reduced config data size
2017-01-27 panel
2017-04-05 Change baud rate to 9600

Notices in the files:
parts and their libraries:
SparkFun-Aesthetics: Licensing: Creative Commons ShareAlike 4.0 International - https://creativecommons.org/licenses/by-sa/4.0
SparkFun-Aesthetics: Released under the Creative Commons Attribution Share-Alike 4.0 License
SparkFun-Aesthetics: https://creativecommons.org/licenses/by-sa/4.0
